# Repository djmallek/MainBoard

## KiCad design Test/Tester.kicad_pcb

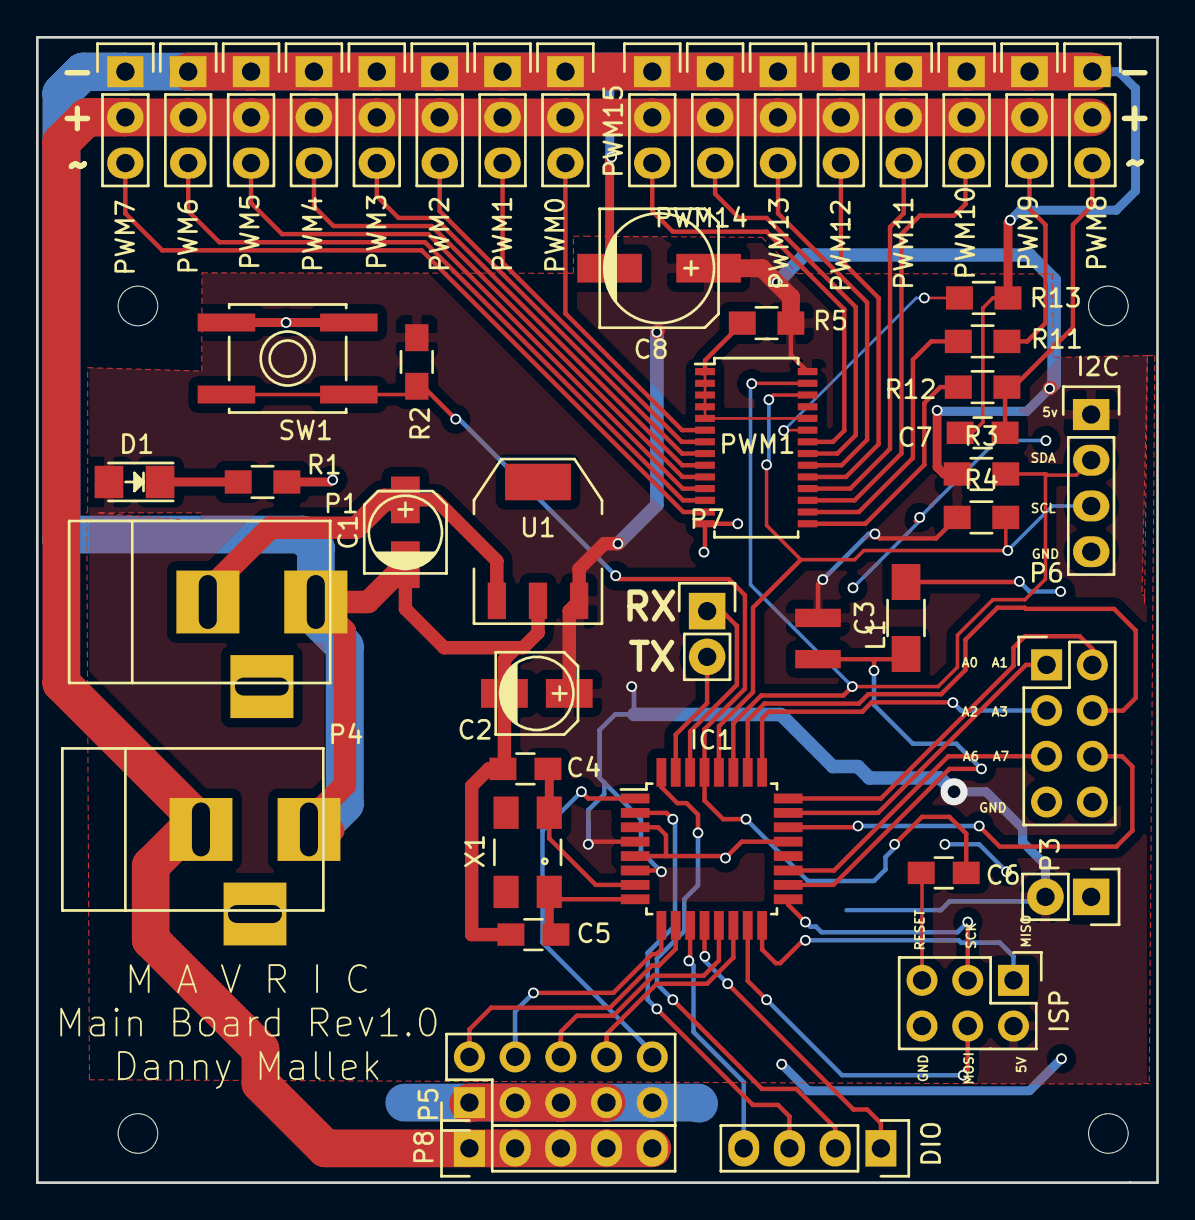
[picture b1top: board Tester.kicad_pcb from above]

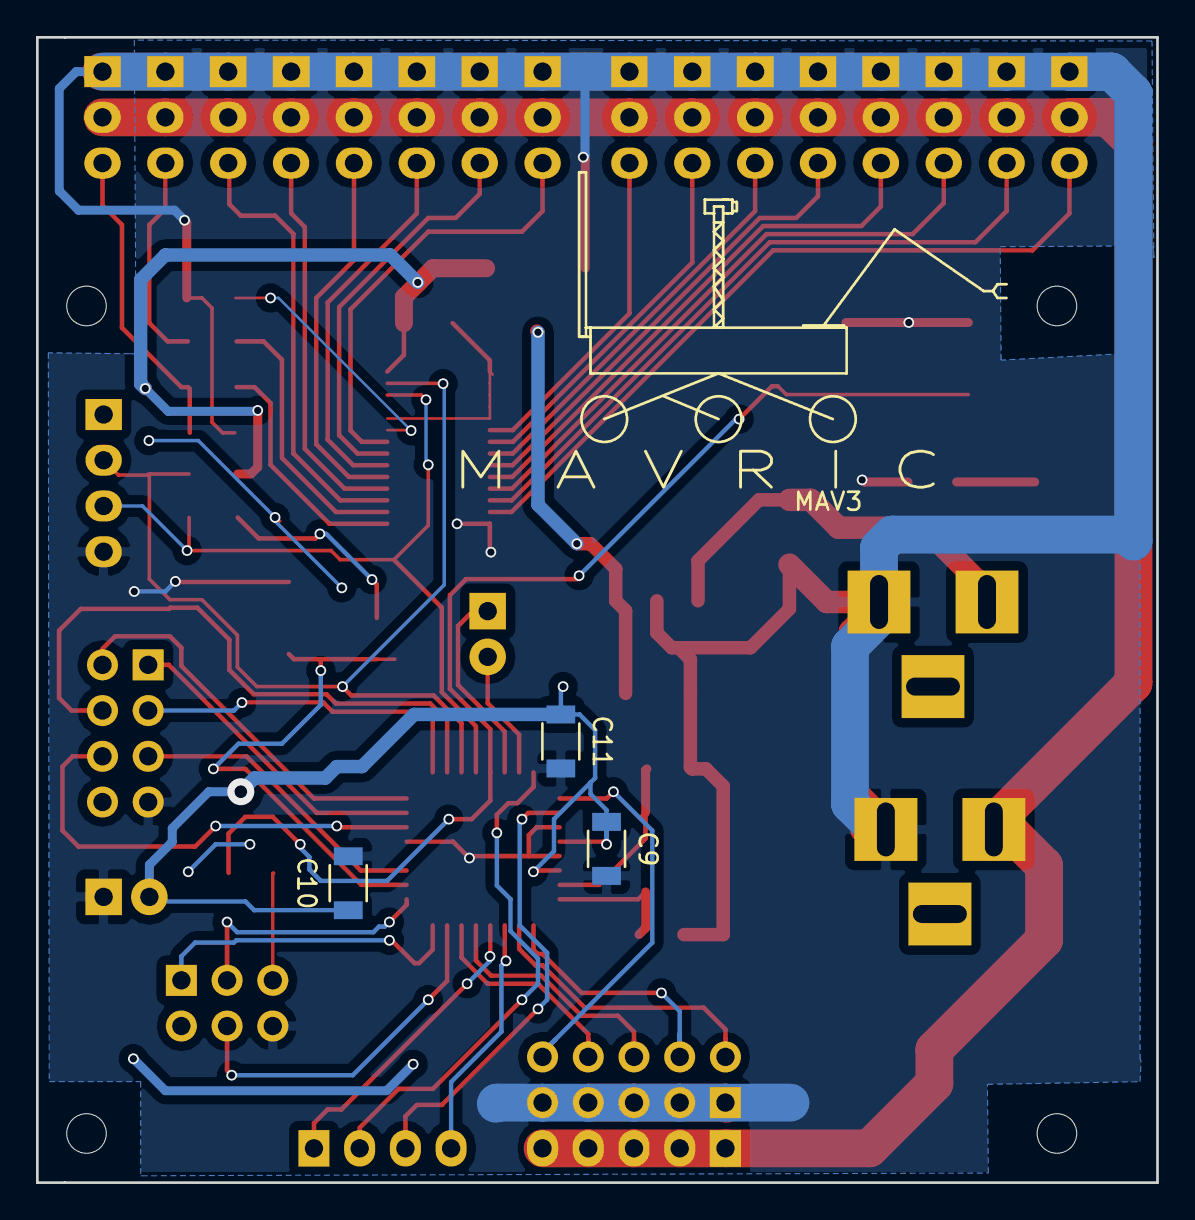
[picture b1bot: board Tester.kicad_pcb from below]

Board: 2 copper layers, 62.2 x 63.6 mm, 53 parts (4 on the bottom side), 52 nets.

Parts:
C1, C2: 10u; c_elec_4x4.5
C3: 100n; C_1206_HandSoldering
C4, C5: 22p; C_0805_HandSoldering
C6: 100n; C_0805_HandSoldering
C7: 100nf; C_0805_HandSoldering
C8: 150u; c_elec_6.3x5.8
C9: 4.7u; C_1206
C10, C11: 100n; C_1206
D1: LED; LED_1206
DIO: DIO Port; Pin_Header_Straight_1x04
I2C: I2C BUS; Pin_Header_Straight_1x04
IC1: ATMEGA328-A; TQFP-32_7x7mm_Pitch0.8mm
ISP: ISP; Pin_Header_Straight_2x03
L1: 10u; Neosid_Inductor_SM-NE29_SMD1008
MAV3: MAVRIC
P1: 7-16v; BARREL_JACK
P3: 5vReg; Pin_Header_Straight_1x02
P4: Servo Power; BARREL_JACK
P5: PMW; Pin_Header_Straight_2x05
P6: Analog Port; Pin_Header_Straight_2x04
P7: RS232; Pin_Header_Straight_1x02
P8: Servo Power 1; Pin_Header_Straight_1x05
PWM0: PWM0; Pin_Header_Straight_1x03
PWM1: PCA9685; TSSOP-28_4.4x9.7mm_Pitch0.65mm
PWM1#2: PWM1; Pin_Header_Straight_1x03
PWM2: PWM2; Pin_Header_Straight_1x03
PWM3: PWM3; Pin_Header_Straight_1x03
PWM4: PWM4; Pin_Header_Straight_1x03
PWM5: PWM5; Pin_Header_Straight_1x03
PWM6: PWM6; Pin_Header_Straight_1x03
PWM7: PWM7; Pin_Header_Straight_1x03
PWM8: PWM8; Pin_Header_Straight_1x03
PWM9: PWM9; Pin_Header_Straight_1x03
PWM10: PWM10; Pin_Header_Straight_1x03
PWM11: PWM11; Pin_Header_Straight_1x03
PWM12: PWM12; Pin_Header_Straight_1x03
PWM13: PWM13; Pin_Header_Straight_1x03
PWM14: PWM14; Pin_Header_Straight_1x03
PWM15: PWM15; Pin_Header_Straight_1x03
R1, R11, R12: 220; R_0805_HandSoldering
R2, R5, R13: 10k; R_0805_HandSoldering
R3, R4: 6.8k; R_0805_HandSoldering
SW1: SW_PUSH; SW_SPST_EVQP0
U1: 7805; SOT-223
X1: 16MHz; Crystal_SMD_0603_4Pads

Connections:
+5V: C2.1, C8.1, C9.1, C10.1, C11.1, D1.2, I2C.1, IC1.4, IC1.6, ISP.2, L1.1, P3.2, PWM1.28, R2.1, R3.1, R4.1, R5.2, U1.3
/7.4v: P4.2, P8.1, P8.2, P8.3, P8.4, P8.5, PWM0.2, PWM1#2.2, PWM2.2, PWM3.2, PWM4.2, PWM5.2, PWM6.2, PWM7.2, PWM8.2, PWM9.2, PWM10.2, PWM11.2, PWM12.2, PWM13.2, PWM14.2, PWM15.2
/ADC0: IC1.23, P6.1
/ADC1: IC1.24, P6.2
/ADC2: IC1.25, P6.3
/ADC3: IC1.26, P6.4
/ADC6: IC1.19, P6.5
/ADC7: IC1.22, P6.6
/AddrPull: PWM1.1, PWM1.2, PWM1.3, PWM1.4, PWM1.5, PWM1.24, R5.1
/DIO0: DIO.1, IC1.12
/DIO1: DIO.2, IC1.32
/DIO2: DIO.3, IC1.2
/DIO3: DIO.4, IC1.11
/MISO: IC1.16, ISP.1
/MOSI: IC1.15, ISP.4
/OSC1: C4.2, IC1.7, X1.2
/OSC2: C5.1, IC1.8, X1.1
/PMW0/A: IC1.10, P5.2
/PMW0/B: IC1.9, P5.4
/PWM0: PWM0.3, PWM1.6
/PWM1: PWM1.7, PWM1#2.3
/PWM1/A: IC1.13, P5.6
/PWM1/B: IC1.14, P5.8
/PWM2: PWM1.8, PWM2.3
/PWM2/B: IC1.1, P5.10
/PWM3: PWM1.9, PWM3.3
/PWM4: PWM1.10, PWM4.3
/PWM5: PWM1.11, PWM5.3
/PWM6: PWM1.12, PWM6.3
/PWM7: PWM1.13, PWM7.3
/PWM8: C7.1, PWM8.3, R12.1
/PWM9: PWM9.3, R11.1
/PWM10: PWM1.17, PWM10.3
/PWM11: PWM1.18, PWM11.3
/PWM12: PWM1.19, PWM12.3
/PWM13: PWM1.20, PWM13.3
/PWM14: PWM1.21, PWM14.3
/PWM15: PWM1.22, PWM15.3
/RX: IC1.30, P7.1
/SCK: IC1.17, ISP.3
/SCL: I2C.3, IC1.28, PWM1.26, R4.2
/SDA: I2C.2, IC1.27, PWM1.27, R3.2
/TX: IC1.31, P7.2
/~RESET: C6.1, IC1.29, R2.2, SW1.1
GND: C1.2, C2.2, C3.2, C4.1, C5.2, C7.2, C8.2, C9.2, C10.2, C11.2, I2C.4, IC1.3, IC1.5, IC1.21, ISP.6, P1.1, P3.1, P4.1, P5.1, P5.3, P5.5, P5.7, P5.9, P6.7, PWM0.1, PWM1.14, PWM1#2.1, PWM2.1, PWM3.1, PWM4.1, PWM5.1, PWM6.1, PWM7.1, PWM8.1, PWM9.1, PWM10.1, PWM11.1, PWM12.1, PWM13.1, PWM14.1, PWM15.1, R1.2, R13.1, SW1.2, U1.2
unnamed: C3.1, IC1.18, L1.2
unnamed: C6.2, ISP.5
unnamed: D1.1, R1.1
unnamed: PWM1.15, R12.2
unnamed: PWM1.16, R11.2
unnamed: PWM1.23, R13.2
VCC: C1.1, P1.2, U1.1

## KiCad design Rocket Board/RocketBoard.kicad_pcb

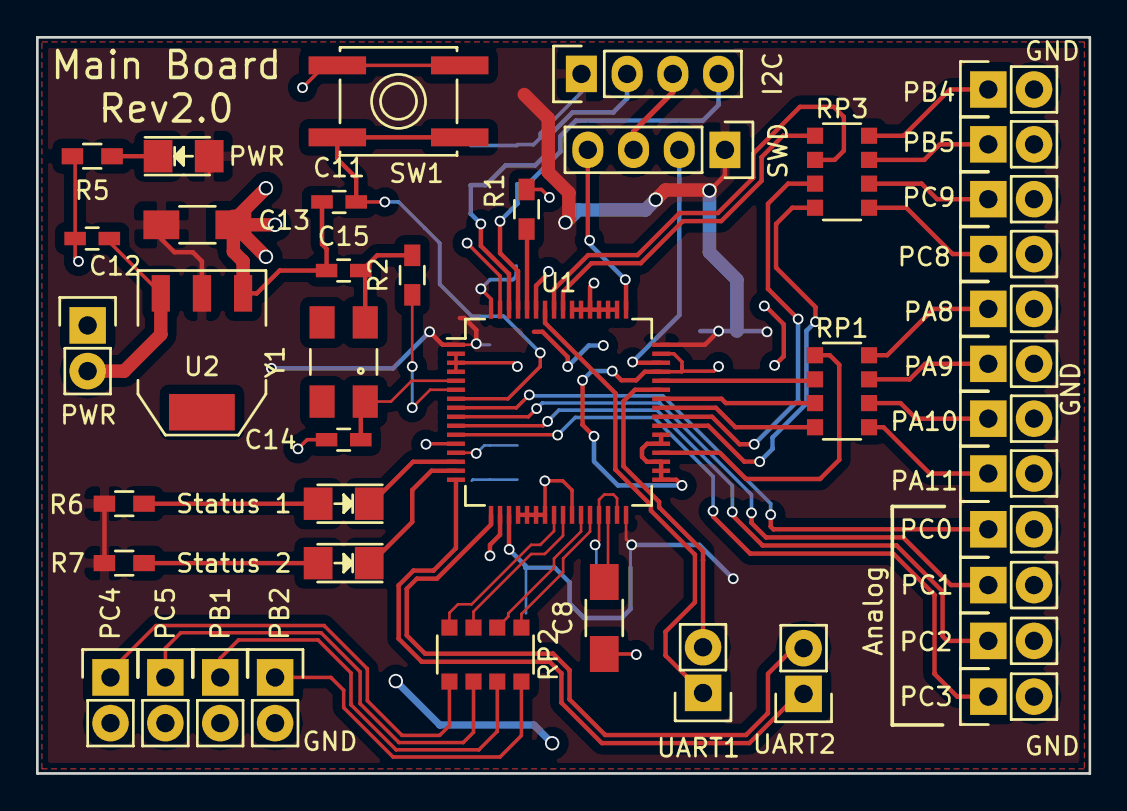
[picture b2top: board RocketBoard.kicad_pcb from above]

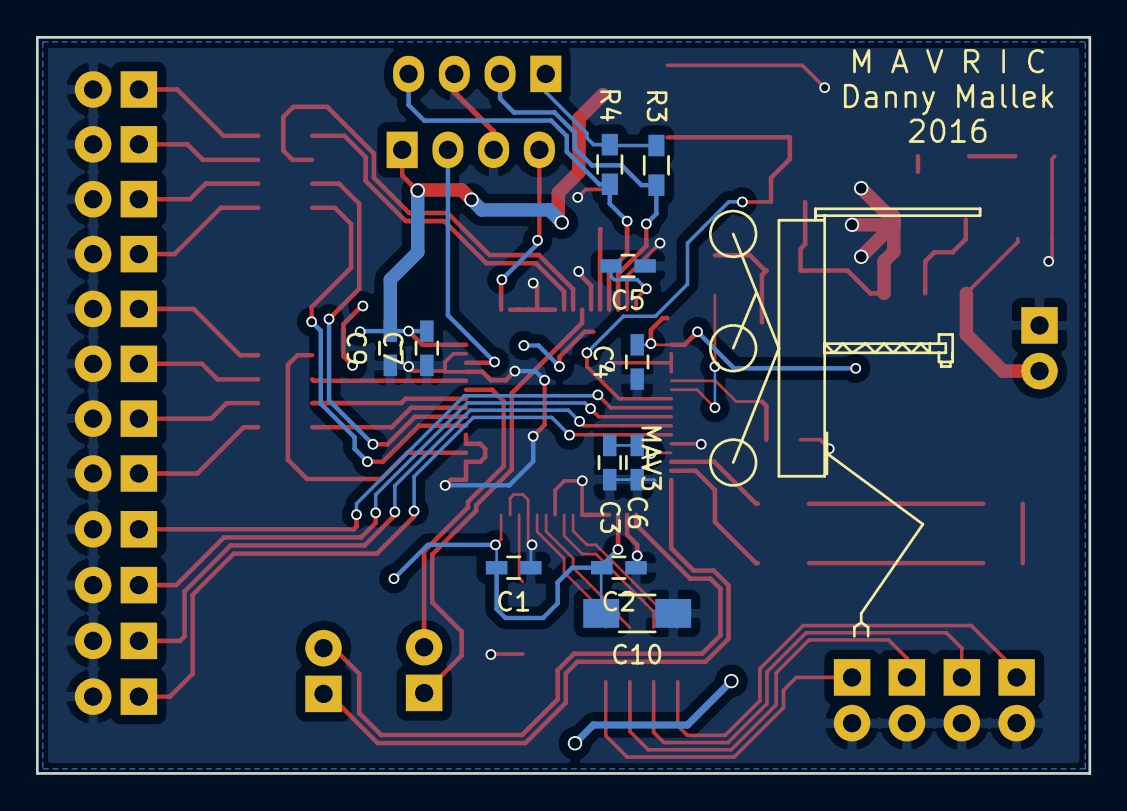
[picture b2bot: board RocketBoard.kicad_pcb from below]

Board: 2 copper layers, 58.5 x 40.9 mm, 54 parts (12 on the bottom side), 51 nets.

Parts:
C1, C2, C3, C4, C5, C7, C9, C12: 100n; C_0603_HandSoldering
C6: 1u; C_0603_HandSoldering
C8, C10: 4.7u; C_1206_HandSoldering
C11: 0.1u; C_0603_HandSoldering
C13: 10u; C_1206_HandSoldering
C14, C15: 10p; C_0603_HandSoldering
I2C: I2C; Pin_Header_Straight_1x04
MAV3: MAVRIC
PA8: PA_8; Pin_Header_Straight_1x02
PA9: PA_9; Pin_Header_Straight_1x02
PA10: PA_10; Pin_Header_Straight_1x02
PA11: PA_11; Pin_Header_Straight_1x02
PB1: PB_1; Pin_Header_Straight_1x02
PB2: PB_2; Pin_Header_Straight_1x02
PB4: PB_4; Pin_Header_Straight_1x02
PB5: PB_5; Pin_Header_Straight_1x02
PC0: PC_0; Pin_Header_Straight_1x02
PC1: PC_1; Pin_Header_Straight_1x02
PC2: PC_2; Pin_Header_Straight_1x02
PC3: PC_3; Pin_Header_Straight_1x02
PC4: PC_4; Pin_Header_Straight_1x02
PC5: PC_5; Pin_Header_Straight_1x02
PC8: PC_8; Pin_Header_Straight_1x02
PC9: PC_9; Pin_Header_Straight_1x02
PWR: Power; LED_1206
PWR#2: Power; Pin_Header_Straight_1x02
R1: 10k; R_0603_HandSoldering
R2: R_Ext; R_0603_HandSoldering
R3, R4: 4.7k; R_0603_HandSoldering
R5, R6, R7: 220; R_0603_HandSoldering
RP1, RP2, RP3: 220 4pack; R_Array_Convex_4x1206
SW1: SPST; SW_SPST_EVQP0
SWD: SWD; Pin_Header_Straight_1x04
Status 1: Status1; LED_1206
Status 2: Status2; LED_1206
U1: STM32F401RCT6; LQFP-64_10x10mm_Pitch0.5mm
U2: LD1117S33TR; SOT-223
UART1: UART1; Pin_Header_Straight_1x02
UART2: UART2; Pin_Header_Straight_1x02
Y1: 25MHz; Crystal_SMD_0603_4Pads

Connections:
+3V3: C1.2, C2.2, C4.2, C5.2, C7.2, C9.2, C10.2, C13.1, I2C.1, PWR.2, R3.1, R4.1, R6.1, R7.1, SWD.1, U1.1, U1.19, U1.32, U1.48, U1.64, U2.2
+12V: C12.1, PWR#2.2, U2.3
/BOOT0: R1.1, U1.60
/NRST: C11.2, SW1.1, U1.7
/OSC1: C14.1, U1.5, Y1.1
/OSC2: R2.1, U1.6
/PA_0: Status 1.1, U1.14
/PA_1: Status 2.1, U1.15
/PA_8: RP1.4, U1.41
/PA_9: RP1.3, U1.42
/PA_11: RP1.2, U1.44
/PB_1: RP2.2, U1.27
/PB_2: RP2.1, U1.28
/PB_4: RP3.1, U1.56
/PB_5: RP3.2, U1.57
/PB_15: RP1.1, U1.36
/PC_0: PC0.1, U1.8
/PC_1: PC1.1, U1.9
/PC_2: PC2.1, U1.10
/PC_3: PC3.1, U1.11
/PC_4: RP2.4, U1.24
/PC_5: RP2.3, U1.25
/PC_8: RP3.4, U1.39
/PC_9: RP3.3, U1.40
/RX1: U1.43, UART1.2
/RX2: U1.17, UART2.2
/SCL_1: I2C.4, R4.2, U1.61
/SDA_1: I2C.2, R3.2, U1.62
/SWCLK: SWD.4, U1.49
/SWDIO: SWD.2, U1.46
/TX1: U1.58, UART1.1
/TX2: U1.16, UART2.1
/VCAP1: C8.2, U1.30
/VDDA: C3.2, C6.2, U1.13
GND: C1.1, C2.1, C3.1, C4.1, C5.1, C6.1, C7.1, C8.1, C9.1, C10.1, C11.1, C12.2, C13.2, C14.2, C15.1, I2C.3, PA8.2, PA9.2, PA10.2, PA11.2, PB1.2, PB2.2, PB4.2, PB5.2, PC0.2, PC1.2, PC2.2, PC3.2, PC4.2, PC5.2, PC8.2, PC9.2, PWR#2.1, R1.2, R5.2, SW1.2, SWD.3, U1.2, U1.3, U1.4, U1.12, U1.18, U1.20, U1.21, U1.22, U1.23, U1.26, U1.29, U1.31, U1.33, U1.34, U1.35, U1.37, U1.38, U1.45, U1.47, U1.50, U1.51, U1.52, U1.53, U1.54, U1.55, U1.59, U1.63, U2.1
unnamed: C15.2, R2.2, Y1.2
unnamed: PWR.1, R5.1
unnamed: R6.2, Status 1.2
unnamed: R7.2, Status 2.2
unnamed: PA8.1, RP1.8
unnamed: PA9.1, RP1.7
unnamed: PA10.1, RP1.6
unnamed: PA11.1, RP1.5
unnamed: PB2.1, RP2.8
unnamed: PB1.1, RP2.7
unnamed: PC5.1, RP2.6
unnamed: PC4.1, RP2.5
unnamed: PB4.1, RP3.8
unnamed: PB5.1, RP3.7
unnamed: PC9.1, RP3.6
unnamed: PC8.1, RP3.5

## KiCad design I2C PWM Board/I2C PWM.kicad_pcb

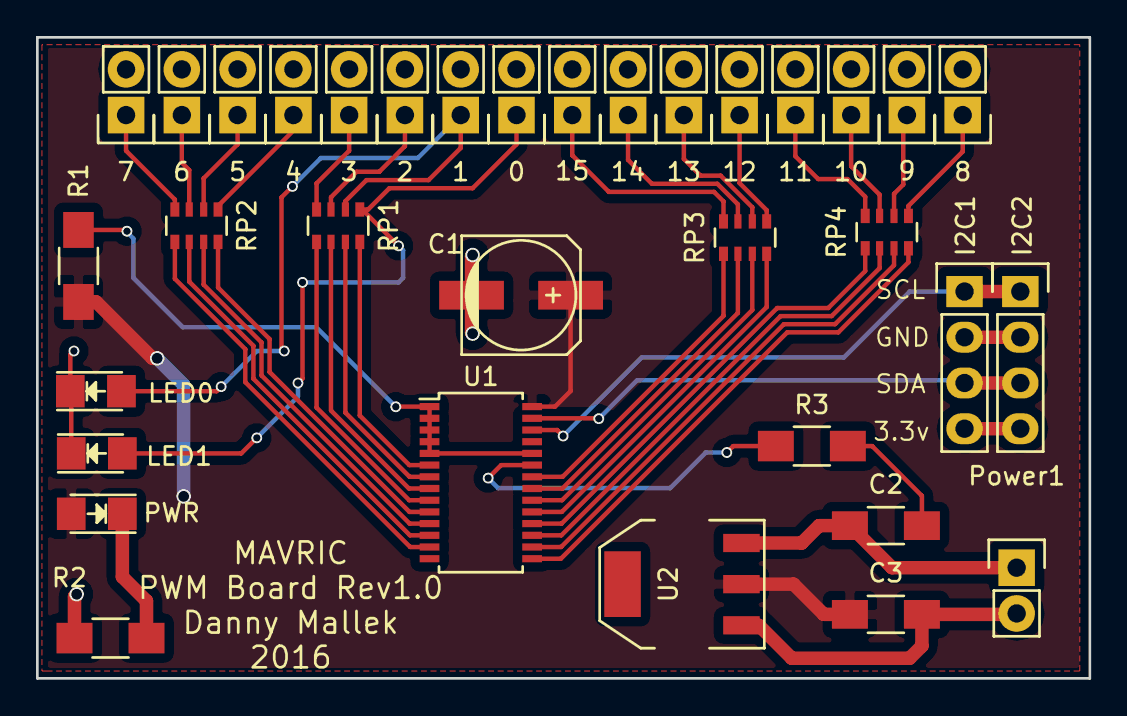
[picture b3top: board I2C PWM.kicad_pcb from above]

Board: 2 copper layers, 58.5 x 35.6 mm, 35 parts (1 on the bottom side), 42 nets.

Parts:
0: PWM0; Pin_Header_Straight_1x02
1: PWM1; Pin_Header_Straight_1x02
2: PWM2; Pin_Header_Straight_1x02
3: PWM3; Pin_Header_Straight_1x02
4: PWM4; Pin_Header_Straight_1x02
5: PWM5; Pin_Header_Straight_1x02
6: PWM6; Pin_Header_Straight_1x02
7: PWM7; Pin_Header_Straight_1x02
8: PWM8; Pin_Header_Straight_1x02
9: PWM9; Pin_Header_Straight_1x02
10: PWM10; Pin_Header_Straight_1x02
11: PWM11; Pin_Header_Straight_1x02
12: PWM12; Pin_Header_Straight_1x02
13: PWM13; Pin_Header_Straight_1x02
14: PWM14; Pin_Header_Straight_1x02
15: PWM15; Pin_Header_Straight_1x02
C1: 150u; c_elec_6.3x5.8
C2: 100n; C_1206_HandSoldering
C3: 10u; C_1206_HandSoldering
I2C1, I2C2: I2C; Pin_Header_Straight_1x04
LED0, LED1: LED; LED_1206
MAV3: MAVRIC
PWR: LED; LED_1206
Power1: Power; Pin_Header_Straight_1x02
R1, R3: 10k; R_1206_HandSoldering
R2: 220; R_1206_HandSoldering
RP1, RP2, RP3, RP4: R_PACK4; R_Array_Convex_4x0603
U1: PCA9685; TSSOP-28_4.4x9.7mm_Pitch0.65mm
U2: LD1117S33TR; SOT-223

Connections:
+3V3: C1.1, C3.1, PWR.2, R1.1, U1.28, U2.2
+12V: C2.1, Power1.1, U2.3
/3.3vPass: I2C1.4, I2C2.4
/AddrPull: R1.2, U1.1, U1.2, U1.3, U1.4, U1.5, U1.24
/GNDPass: I2C1.2, I2C2.2
/PWM0: 0.1, LED1.2, RP1.1
/PWM1: 1.1, LED0.2, RP1.2
/PWM2: 2.1, RP1.3
/PWM3: 3.1, RP1.4
/PWM4: 4.1, RP2.1
/PWM5: 5.1, RP2.2
/PWM6: 6.1, RP2.3
/PWM7: 7.1, RP2.4
/PWM8: 8.1, RP4.5
/PWM9: 9.1, RP4.6
/PWM10: 10.1, RP4.7
/PWM11: 11.1, RP4.8
/PWM12: 12.1, RP3.5
/PWM13: 13.1, RP3.6
/PWM14: 14.1, RP3.7
/PWM15: 15.1, RP3.8
/SCL: I2C1.1, I2C2.1, U1.26
/SDA: I2C1.3, I2C2.3, U1.27
GND: 0.2, 1.2, 2.2, 3.2, 4.2, 5.2, 6.2, 7.2, 8.2, 9.2, 10.2, 11.2, 12.2, 13.2, 14.2, 15.2, C1.2, C2.2, C3.2, LED0.1, LED1.1, Power1.2, R2.2, R3.2, U1.14, U2.1
unnamed: PWR.1, R2.1
unnamed: R3.1, U1.23
unnamed: RP1.5, U1.9
unnamed: RP1.6, U1.8
unnamed: RP1.7, U1.7
unnamed: RP1.8, U1.6
unnamed: RP2.5, U1.13
unnamed: RP2.6, U1.12
unnamed: RP2.7, U1.11
unnamed: RP2.8, U1.10
unnamed: RP3.1, U1.22
unnamed: RP3.2, U1.21
unnamed: RP3.3, U1.20
unnamed: RP3.4, U1.19
unnamed: RP4.1, U1.18
unnamed: RP4.2, U1.17
unnamed: RP4.3, U1.16
unnamed: RP4.4, U1.15

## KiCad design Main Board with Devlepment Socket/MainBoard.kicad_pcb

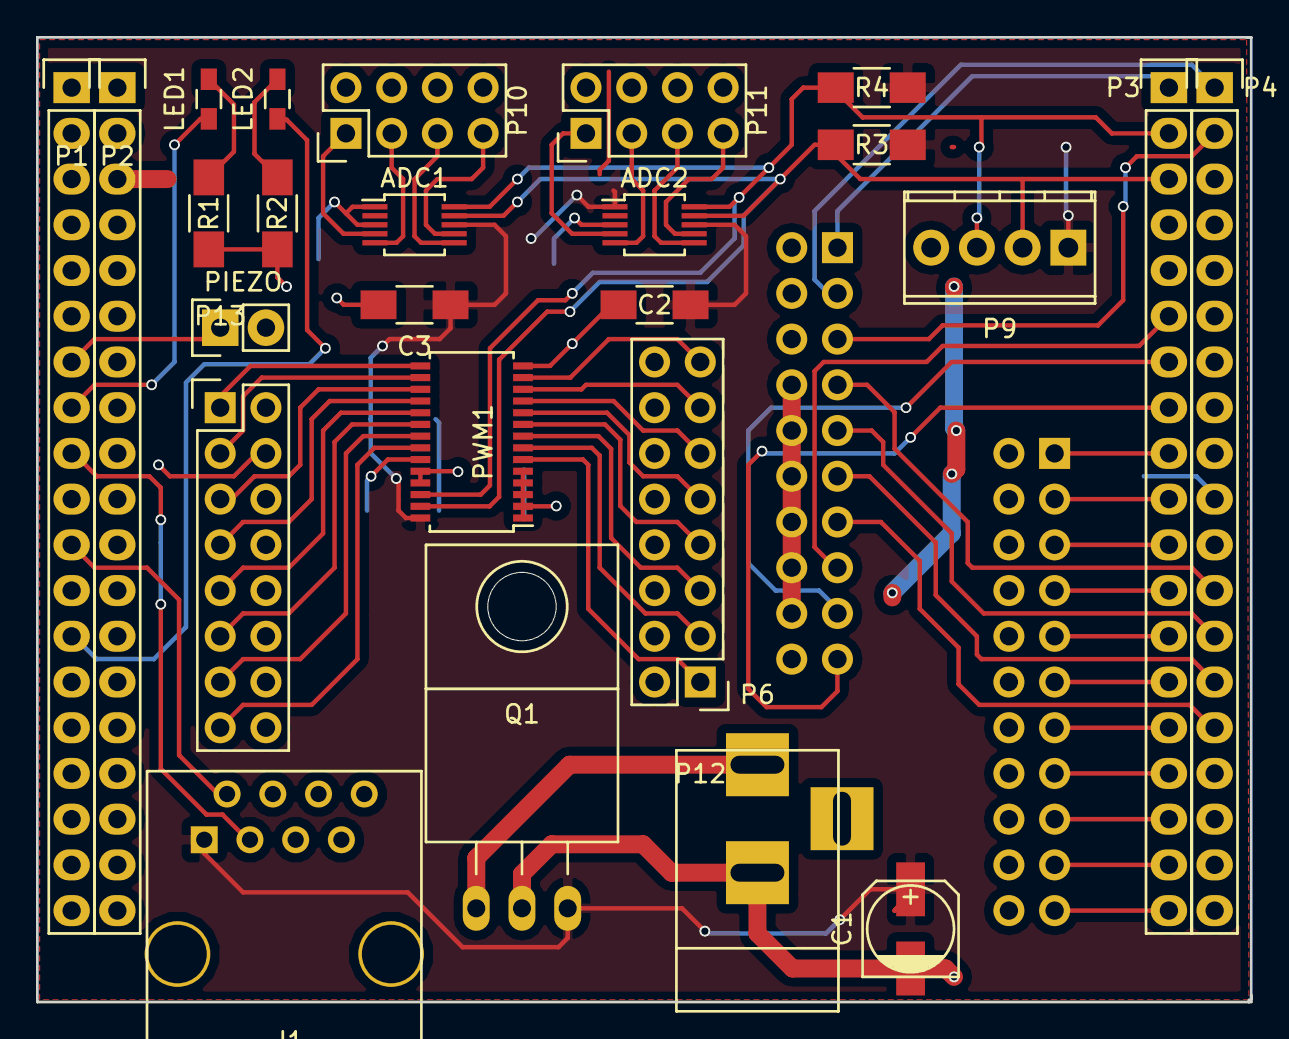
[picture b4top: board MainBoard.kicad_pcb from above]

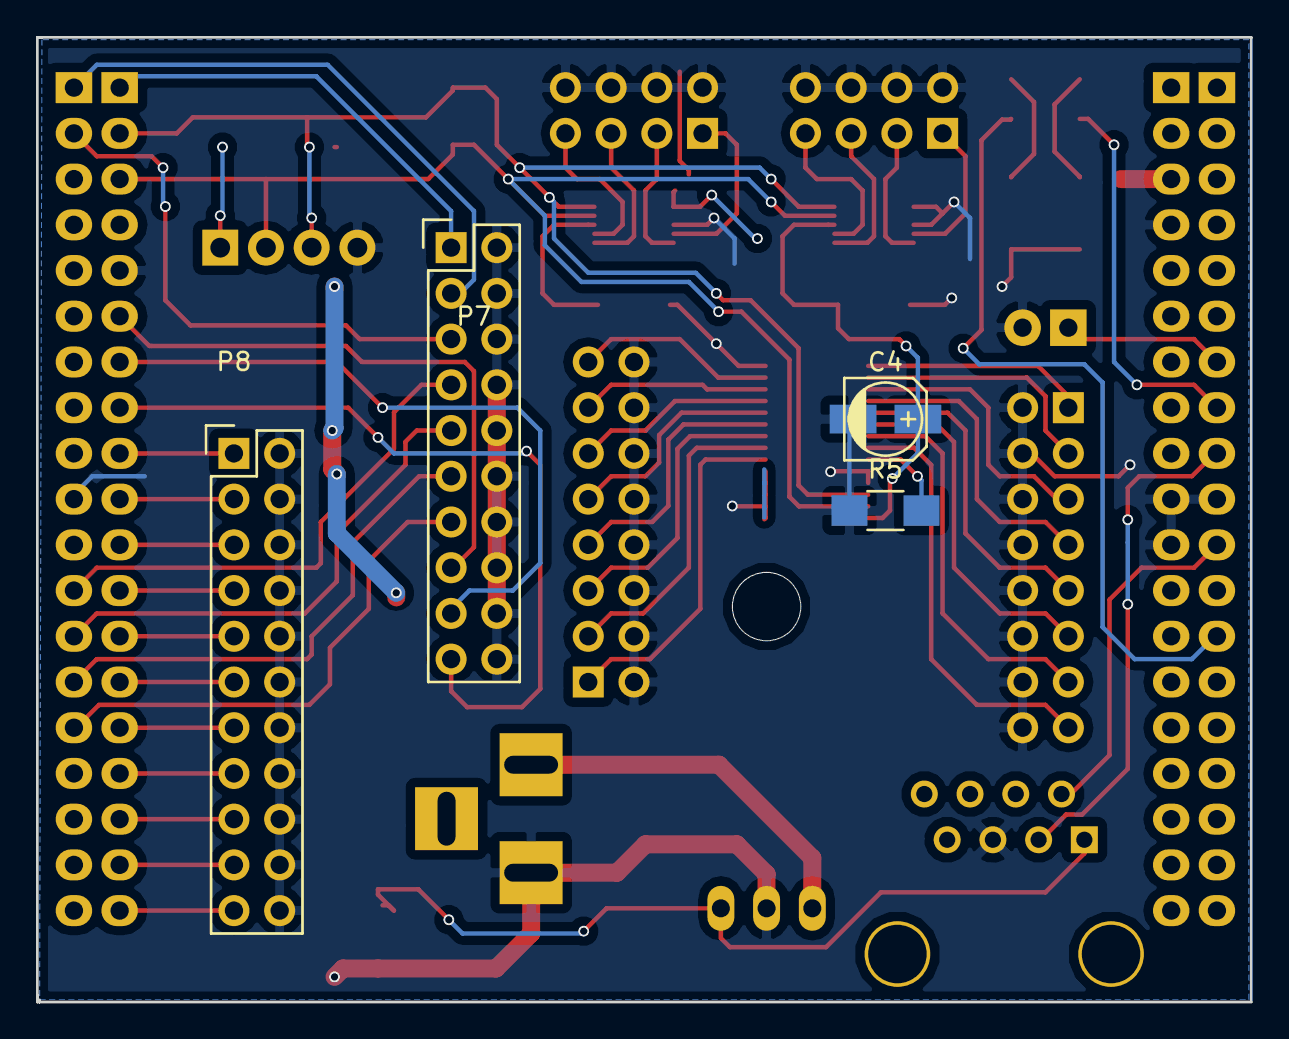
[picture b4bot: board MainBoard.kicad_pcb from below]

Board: 2 copper layers, 67.4 x 53.6 mm, 29 parts (4 on the bottom side), 58 nets.

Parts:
ADC1, ADC2: ADS1015; MSOP-10_3x3mm_Pitch0.5mm
C1: 100u; c_elec_5x5.3
C2, C3: 100n; C_1206_HandSoldering
C4: 10u; c_elec_4x5.3
J1: DB9; RJ45_8
LED1: StatusLED1; R_0603_HandSoldering
LED2: StatusLED2; R_0603_HandSoldering
P1, P2, P3, P4: CONN_01X19; Pin_Header_Straight_1x19
P6: CONN_01X02; BARREL_JACK
P7: CONN_02X10; Pin_Header_Straight_2x10
P8: CONN_02X11; Pin_Header_Straight_2x11
P9: CONN_01X04; TerminalBlock_Pheonix_MPT-2.54mm_4pol
P10, P11: ADC0 Conn; Pin_Header_Straight_2x04
P12, P13: CONN_02X08; Pin_Header_Straight_2x08
PIEZO: PIEZO; Pin_Header_Straight_1x02
PWM1: PCA9685; TSSOP-28_4.4x9.7mm_Pitch0.65mm
Q1: FQP47P06; TO-220_Neutral123_Horizontal
R1, R2: 220; R_1206_HandSoldering
R3, R4: 4.7k; R_1206_HandSoldering
R5: 10K; R_1206_HandSoldering

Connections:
+5V: ADC1.8, ADC2.1, ADC2.8, C1.1, C2.1, C3.1, C4.1, J1.1, P9.1, PWM1.28, Q1.3, R3.1, R4.1
/I2C_Bus/AIN0_0: ADC1.4, P10.1
/I2C_Bus/AIN0_1: ADC1.5, P10.3
/I2C_Bus/AIN0_2: ADC1.6, P10.5
/I2C_Bus/AIN0_3: ADC1.7, P10.7
/I2C_Bus/AIN1_0: ADC2.4, P11.1
/I2C_Bus/AIN1_1: ADC2.5, P11.3
/I2C_Bus/AIN1_2: ADC2.6, P11.5
/I2C_Bus/AIN1_3: ADC2.7, P11.7
/I2C_Bus/PWM0: P12.1, PWM1.6
/I2C_Bus/PWM1: P12.3, PWM1.7
/I2C_Bus/PWM2: P12.5, PWM1.8
/I2C_Bus/PWM3: P12.7, PWM1.9
/I2C_Bus/PWM4: P12.9, PWM1.10
/I2C_Bus/PWM5: P12.11, PWM1.11
/I2C_Bus/PWM6: P12.13, PWM1.12
/I2C_Bus/PWM7: P12.15, PWM1.13
/I2C_Bus/PWM8: P13.1, PWM1.15
/I2C_Bus/PWM9: P13.3, PWM1.16
/I2C_Bus/PWM10: P13.5, PWM1.17
/I2C_Bus/PWM11: P13.7, PWM1.18
/I2C_Bus/PWM12: P13.9, PWM1.19
/I2C_Bus/PWM13: P13.11, PWM1.20
/I2C_Bus/PWM14: P13.13, PWM1.21
/I2C_Bus/PWM15: P13.15, PWM1.22
/I2C_Bus/SCL: ADC1.10, ADC2.10, P3.2, P9.3, PWM1.26, R4.2
/I2C_Bus/SDA: ADC1.9, ADC2.9, P3.3, P9.2, PWM1.27, R3.2
/PA_2: P3.18, P8.19
/PA_3: P3.19, P8.21
/PA_5: P3.6, P7.15
/PA_6: P3.7, P7.17
/PA_7: P3.8, P7.19
/PA_8: P3.12, P8.7
/PA_9: P3.11, P8.5
/PA_10: P3.17, P8.17
/PA_13: P1.7, PIEZO.1
/PA_14: LED1.2, P1.8
/PA_15: J1.3, P1.9
/PB_1: P4.12, P7.7
/PB_3: P3.16, P8.15
/PB_4: P3.14, P8.11
/PB_5: P3.15, P8.13
/PB_6: P3.9, P8.1
/PB_7: J1.2, P1.11
/PB_10: P3.13, P8.9
/PB_13: P4.15, P7.13
/PB_14: P4.14, P7.11
/PB_15: P4.13, P7.9
/PC_6: P4.2, P7.5
/PC_7: P3.10, P8.3
/PC_8: P4.1, P7.3
/PC_9: P3.1, P7.1
/PC_14: LED2.2, P1.13
GND: ADC1.1, ADC1.3, ADC2.3, C1.2, C2.2, C3.2, C4.2, J1.5, P1.10, P2.4, P2.10, P2.11, P3.5, P4.10, P6.2, P7.2, P7.4, P7.6, P7.8, P7.10, P7.12, P7.14, P7.16, P7.18, P7.20, P8.2, P8.4, P8.6, P8.8, P8.10, P8.12, P8.14, P8.16, P8.18, P8.20, P8.22, P9.4, P10.2, P10.4, P10.6, P10.8, P11.2, P11.4, P11.6, P11.8, P12.2, P12.4, P12.6, P12.8, P12.10, P12.12, P12.14, P12.16, P13.2, P13.4, P13.6, P13.8, P13.10, P13.12, P13.14, P13.16, PIEZO.2, PWM1.1, PWM1.2, PWM1.3, PWM1.4, PWM1.5, PWM1.14, PWM1.24, PWM1.25, Q1.2, R1.2, R2.2, R5.1
unnamed: LED1.1, R1.1
unnamed: LED2.1, R2.1
unnamed: P6.1, Q1.1
unnamed: PWM1.23, R5.2

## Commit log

2016-03-25 :octocat: Added .gitattributes
2016-03-25 Initial Commit. Main board designed to sit on Nucleo with breakours for pins and expansion for PWM and ADC using I2C
2016-06-25 Initial Commit Test Board
    The test board is a test PCB for creating a MCU for MAVRIC in KiCAD
2016-06-25 Add connections, Add board marks
2016-07-02 Initial Rocket Board Commit
    Rocket Board dev board. First test with STM32F401RCT6. Features 2 test
    LEDs, 8 PWM output lines, 4 Analog input, 4 ADC, 1 I2C bus, and SWD
    programming
2016-07-05 Partial Layout of Board
    Started the board layout process
2016-07-10 Finish Layout
2016-07-10 Fix analog input, Add 2 UART ports, changed PWM1/3 to PWM1/3N
    Removed the series resistors for analog inputs, added pinouts for
    UART1,2. Changed PWM 1/3 tp PWM 1/3N to free up RX1 pin
2016-07-11 Add and Complete I2C-PWM Board
    I2C Board that fits slots
2016-07-11 Actually Add I2C-PWM Board
2016-07-12 Fix power distribution issues on main board, initial soil board commit
2016-07-16 Create Analog Sensor Board, Add Conglomerate1 Board (Advanced Circuits Order)
